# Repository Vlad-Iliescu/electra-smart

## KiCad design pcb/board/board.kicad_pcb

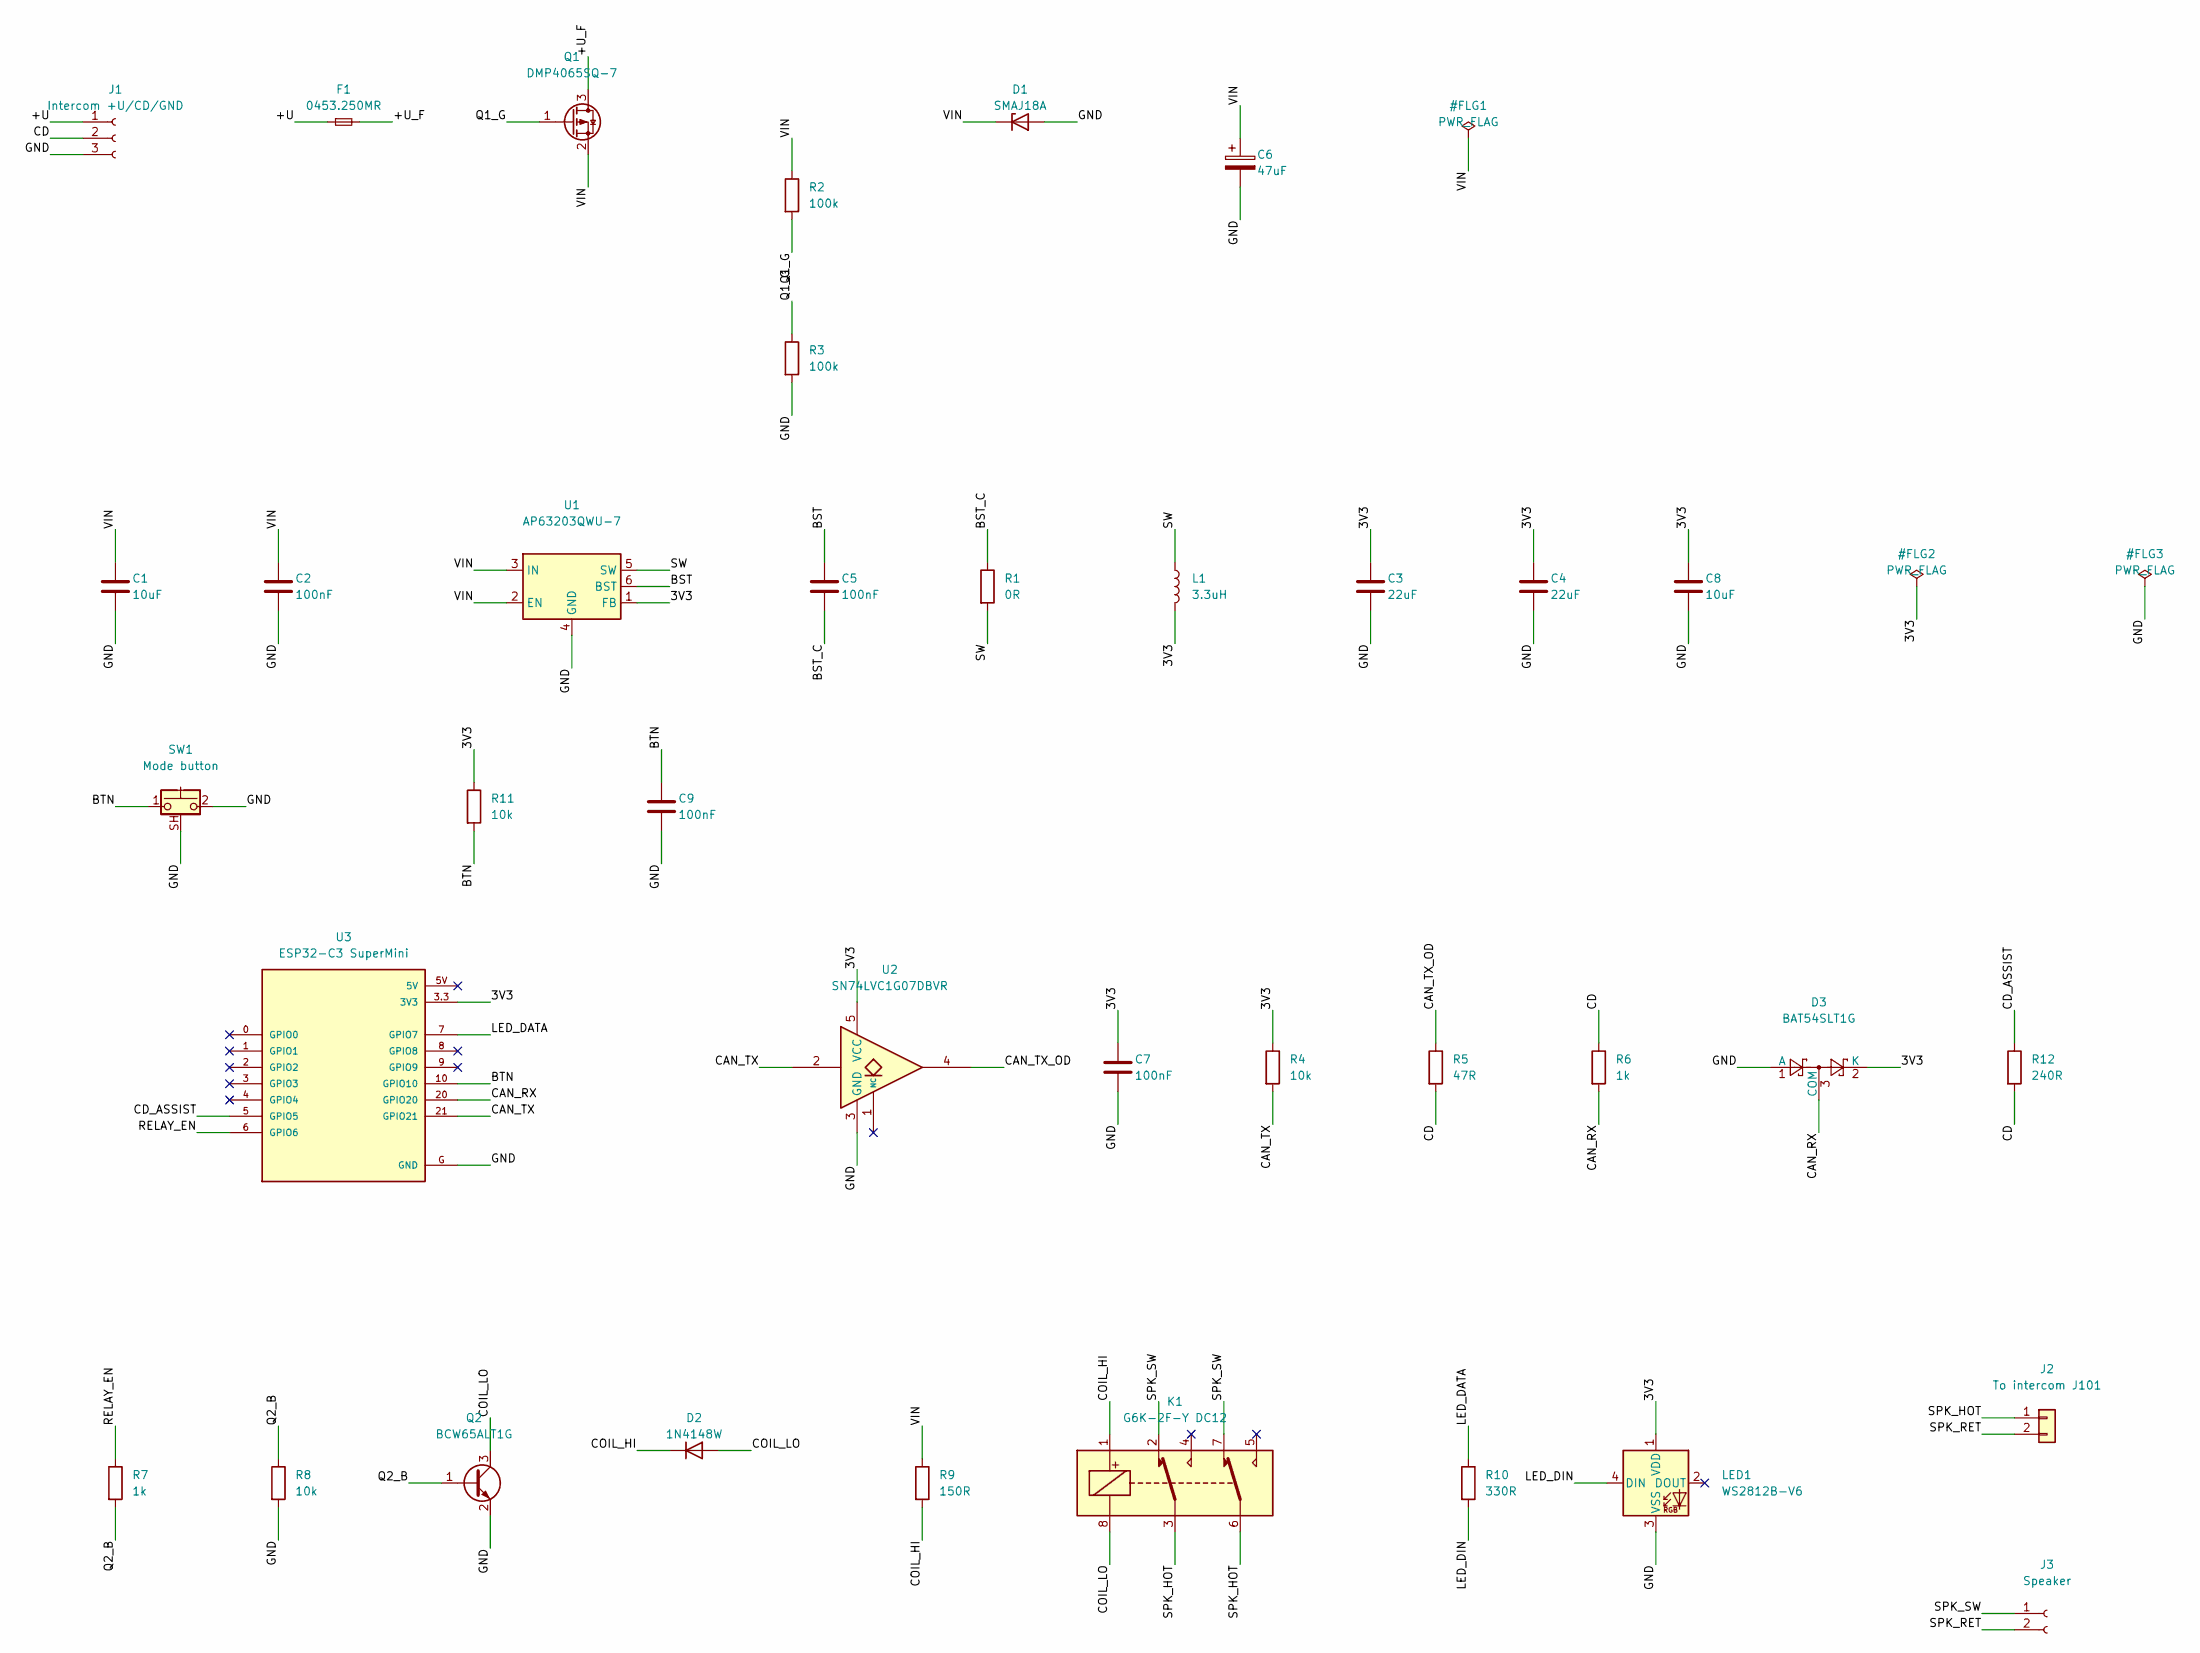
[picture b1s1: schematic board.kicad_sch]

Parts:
C1, C8: 10uF; C_1206_3216Metric_Pad1.33x1.80mm_HandSolder
C2, C5, C7, C9: 100nF; C_0603_1608Metric_Pad1.08x0.95mm_HandSolder
C3, C4: 22uF; C_1210_3225Metric_Pad1.33x2.70mm_HandSolder
C6: 47uF; Capacitor_Panasonic_EEH-ZA_6.3x5.8
D1: SMAJ18A; D_SMA
D2: 1N4148W; D_SOD-123
D3: BAT54SLT1G; SOT-23
F1: 0453.250MR; Fuse_2410_6125Metric_Littelfuse_453
J1: Intercom +U/CD/GND; Conn_MicroJST1.25-SHstyle_1x03-1MP_P1.25mm_Vertical_SMD
J2: To intercom J101; SolderWire-0.15sqmm_1x02_P4mm_D0.5mm_OD1.5mm_Relief
J3: Speaker; Conn_MicroJST1.25-SHstyle_1x02-1MP_P1.25mm_Vertical_SMD
K1: G6K-2F-Y DC12; Relay_DPDT_Omron_G6K-2F-Y
L1: 3.3uH; Inductor_Coilcraft_XGL4020
LED1: WS2812B-V6; LED_WS2812B_PLCC4_5.0x5.0mm_P3.2mm
Q1: DMP4065SQ-7; SOT-23
Q2: BCW65ALT1G; SOT-23
R1: 0R; R_0603_1608Metric_Pad0.98x0.95mm_HandSolder
R2, R3: 100k; R_0603_1608Metric_Pad0.98x0.95mm_HandSolder
R4, R8, R11: 10k; R_0603_1608Metric_Pad0.98x0.95mm_HandSolder
R5: 47R; R_0603_1608Metric_Pad0.98x0.95mm_HandSolder
R6, R7: 1k; R_0603_1608Metric_Pad0.98x0.95mm_HandSolder
R9: 150R; R_0603_1608Metric_Pad0.98x0.95mm_HandSolder
R10: 330R; R_0603_1608Metric_Pad0.98x0.95mm_HandSolder
R12: 240R; R_0603_1608Metric_Pad0.98x0.95mm_HandSolder
SW1: Mode button; SW_Push_Side_CTS_225B_7.8x3.5mm_Boss
U1: AP63203QWU-7; TSOT-23-6
U2: SN74LVC1G07DBVR; SOT-23-5
U3: ESP32-C3 SuperMini; MODULE_ESP32-C3_SUPERMINI

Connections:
/3V3: C3.1, C4.1, C7.1, C8.1, D3.2 (K), L1.2, LED1.1 (VDD), R4.1, R11.1, U1.1 (FB), U2.5 (VCC), U3.3.3 (3V3)
/+U: F1.1, J1.1
/+U_F: F1.2, Q1.3 (D)
/BST: C5.1, U1.6 (BST)
/BST_C: C5.2, R1.1
/BTN: C9.1, R11.2, SW1.1, U3.10 (GPIO10)
/CAN_RX: D3.3 (COM), R6.2, U3.20 (GPIO20)
/CAN_TX: R4.2, U2.2, U3.21 (GPIO21)
/CAN_TX_OD: R5.1, U2.4
/CD: J1.2, R5.2, R6.1, R12.2
/CD_ASSIST: R12.1, U3.5 (GPIO5)
/COIL_HI: D2.1 (K), K1.1, R9.2
/COIL_LO: D2.2 (A), K1.8, Q2.3 (C)
/GND: C1.2, C2.2, C3.2, C4.2, C6.2, C7.2, C8.2, C9.2, D1.2 (A), D3.1 (A), J1.3, LED1.3 (VSS), Q2.2 (E), R3.2, R8.2, SW1.2, SW1.SH (B), U1.4 (GND), U2.3 (GND), U3.G (GND)
/LED_DATA: R10.1, U3.7 (GPIO7)
/LED_DIN: LED1.4 (DIN), R10.2
/Q1_G: Q1.1 (G), R2.2, R3.1
/Q2_B: Q2.1 (B), R7.2, R8.1
/RELAY_EN: R7.1, U3.6 (GPIO6)
/SPK_HOT: J2.1, K1.3, K1.6
/SPK_RET: J2.2, J3.2
/SPK_SW: J3.1, K1.2, K1.7
/SW: L1.1, R1.2, U1.5 (SW)
/VIN: C1.1, C2.1, C6.1, D1.1 (K), Q1.2 (S), R2.1, R9.1, U1.2 (EN), U1.3 (IN)

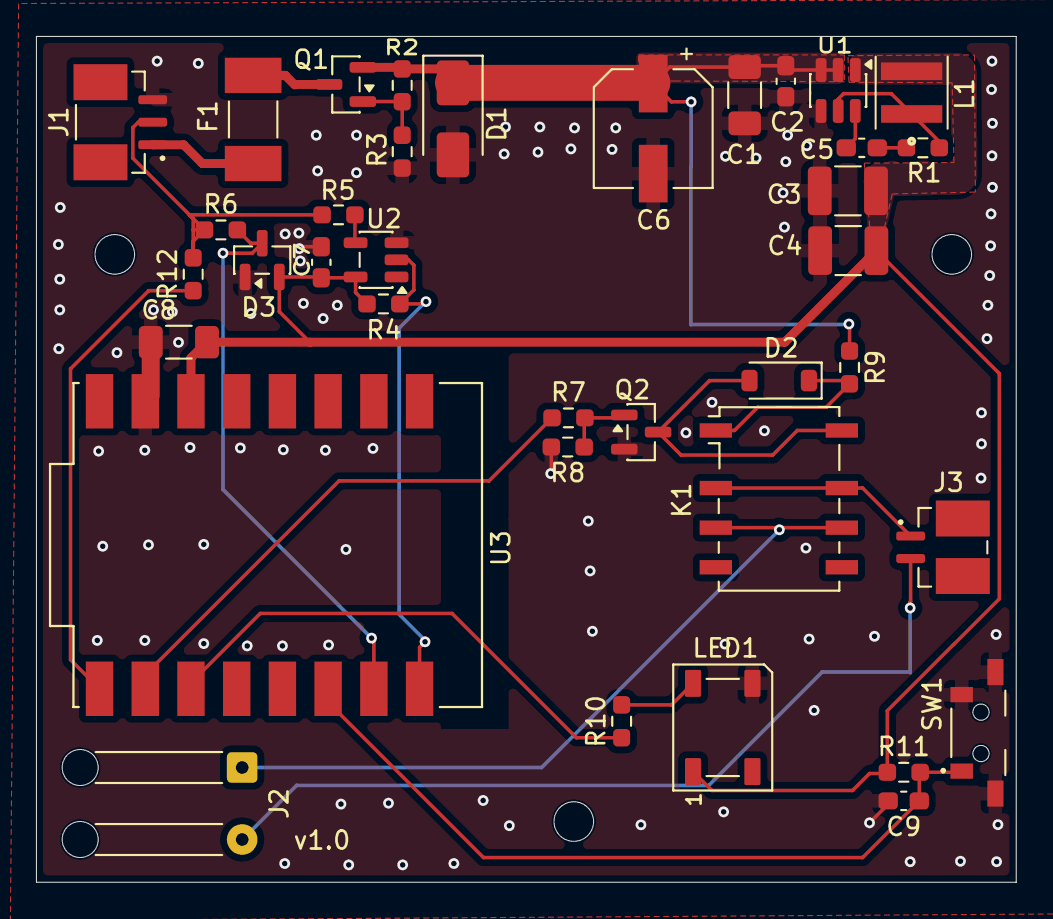
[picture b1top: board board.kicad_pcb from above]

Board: 2 copper layers, 54.4 x 47.0 mm, 40 parts (0 on the bottom side), 24 nets.

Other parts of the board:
H1, H2, H3: MountingHole_2.2mm_M2

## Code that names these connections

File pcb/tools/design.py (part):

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    # a bit is dominant, this resistor is still sourcing into the line against R5,
    # so it lifts the dominant level off ground: ~0.28 V at 1 k, ~0.65 V at 240 R,
    # ~0.78 V at 180 R, against a threshold around 1.5 V. 240 R keeps ~0.9 V of
    # margin and costs GPIO5 11.5 mA while dominant. 180 R buys a slightly faster
    # edge by spending that margin, so it is not a free "if skew is still fat" step.
    'R12': ('Device:R', '240R', R0603, 335, 180, 'right'),
    # --- speaker-mute relay ----------------------------------------------
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
    # TWAI TX out of the ESP32 into the open-drain buffer. R4 holds the line
    # recessive while the ESP32 boots with its GPIOs floating.
    'CAN_TX': [('U3', '21', 'GPIO21'), ('U2', '2', None), ('R4', '2', None)],
    'CAN_TX_OD': [('U2', '4', None), ('R5', '1', None)],

    # The intercom's single-wire CAN bus.
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    # R12 pulls the line up, but only while a frame is going out. Driven
    # permanently it fights whatever holds the bus dominant weakly - that showed
    # up as bursts of ~58 kHz relaxation oscillation - and it would leave a
    # low-value path to a dead rail on shared building wiring. GPIO5 is an input
    # at every other instant, including before setup() runs and while the board is
    # unpowered, which preserves the fail-safe the rest of this design is built on.
    #
    # This is roughly how a single-wire CAN transceiver behaves: recessive is
    # driven, but only by the node that is talking. A transceiver does it better,
    # by following the transmitted bit so it stops sourcing during dominant bits.
    # A 74LVC1G125 with its input on CAN_TX and /OE gated by GPIO5 would reproduce
    # that and let R12 grow again; it was considered and set aside to keep the
    # proven circuit. Revisit only if the dominant margin above becomes a problem.
    'CD_ASSIST': [('U3', '5', 'GPIO5'), ('R12', '1', None)],

    # RX with a series resistor and a BAT54S clamping to the 3V3 rail / GND.
    'CAN_RX': [('R6', '2', None), ('U3', '20', 'GPIO20'), ('D3', '3', 'COM')],

    'RELAY_EN': [('U3', '6', 'GPIO6'), ('R7', '1', None)],
    # R8 holds the base down so the relay cannot chatter while the ESP32 boots.
    'Q2_B': [('R7', '2', None), ('Q2', '1', 'B'), ('R8', '1', None)],
    # Coil polarity MEASURED on a loose part (2 Oct 2026) and on board 1: the
    # G6K is a polarised relay and the Omron drawing (G6K.pdf p.6) marks the
    # coil + on pin 1 and - on pin 8. v0.9 had them the other way round, Q2
    # saturated and ~8 mA flowed, and the relay never moved; the same part on
    # the bench operated with + on pin 1. COIL_HI (+U via R9) is pin 1,
    # COIL_LO (Q2 collector) is pin 8. D2 stays cathode-to-COIL_HI. The symbol
    # has no polarity on its coil pins, so this comment and the assertion
    # below are the only guard.
    'COIL_LO': [('Q2', '3', 'C'), ('K1', '8', None), ('D2', '2', 'A')],
    'COIL_HI': [('K1', '1', None), ('D2', '1', 'K'), ('R9', '2', None)],

    'LED_DATA': [('U3', '7', 'GPIO7'), ('R10', '1', None)],
    'LED_DIN': [('R10', '2', None), ('LED1', '4', 'DIN')],

    # Mode button, active low. GPIO10 has no strapping function on the C3, so
    # holding the button down at power-up cannot put the chip into download
    # mode the way GPIO9 would. R11 defines the pin while the ESP32 boots with
    # its GPIOs floating, and C9 absorbs contact bounce plus whatever ESD comes
    # in through the housing opening the plunger pokes out of.
    'BTN': [
        ('U3', '10', 'GPIO10'), ('R11', '2', None),
        ('SW1', '1', '1'), ('C9', '1', None),
    ],

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    # NO = 4/5. The first revision had NC and NO swapped - an unpowered board
    # would have muted the intercom - which is exactly what the pre-fab meter
    # check exists to catch. Do not "tidy" this back to 4/5.
    'SPK_HOT': [('J2', '1', 'Pin_1'), ('K1', '3', None), ('K1', '6', None)],
    'SPK_SW': [('K1', '2', None), ('K1', '7', None), ('J3', '1', 'Pin_1')],
    'SPK_RET': [('J2', '2', 'Pin_2'), ('J3', '2', 'Pin_2')],
}

# Pins deliberately left open.
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
# K1 is polarised: + on pin 1, - on pin 8 (Omron G6K.pdf p.6). Measured wrong
# on v0.9, so this is checked, not trusted. COIL_HI is the +U side.
assert ('K1', '1') in _pins('COIL_HI') and ('K1', '8') in _pins('COIL_LO'), \
    'K1 coil polarity: +U side (COIL_HI) must be pin 1, Q2 side (COIL_LO) pin 8'
assert ('D2', '1') in _pins('COIL_HI') and ('D2', '2') in _pins('COIL_LO'), \
    'D2 flyback: cathode (pin 1) on COIL_HI, anode (pin 2) on COIL_LO'
# Contacts, measured 23 Aug 2026: NC = 2/7, COM = 3/6, NO = 4/5 open.
assert {('K1', '2'), ('K1', '7')} <= _pins('SPK_SW'), 'K1 NC contacts are 2/7'
assert {('K1', '3'), ('K1', '6')} <= _pins('SPK_HOT'), 'K1 COM contacts are 3/6'
assert {('K1', '4'), ('K1', '5')} <= set(NO_CONNECT), 'K1 NO contacts 4/5 stay open'

PAPER = 'A3'
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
